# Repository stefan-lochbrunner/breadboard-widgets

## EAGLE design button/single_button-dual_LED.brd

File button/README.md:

[**more info**](https://hackaday.io/project/6332-breadboard-widgets/log/19614-button-w-pull-updown)

#### single button
Small board that incorporates a button and pull-resistor. Can be plugged into power rails. Depending on which side of a breadboard it is plugged in, acts as pull-up or pull-down. Optional footprints for low-pass filter for debouncing.

#### single button with SMD LED breakout
added over complicated LED breakout to utilize board space. Also added arrow to indicate pull direction.

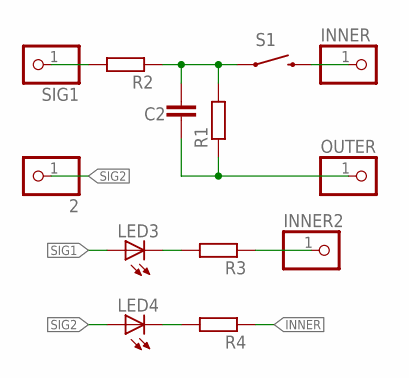
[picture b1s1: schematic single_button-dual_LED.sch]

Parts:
2: PINHD-1X1CB; 1X01-CLEANBIG
C2: CAPACITOR_NPOL-0805; C805
INNER, INNER2: PINHD-1X1CB; 1X01-CLEANBIG
LED3, LED4: LED-0805; LED-805
OUTER: PINHD-1X1CB; 1X01-CLEANBIG
R1, R2, R3, R4: RESISTORR805-0805; R805
S1: SWITCH-MOMENTARY-2PTH; TACTILE-PTH
SIG1: PINHD-1X1CB; 1X01-CLEANBIG

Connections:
INNER: INNER.1, R4.1, S1.3 (2), S1.4 (2)
unnamed: C2.1, R1.2, R2.1, S1.1, S1.2 (1)
unnamed: LED4.C, R4.2
unnamed: LED3.C, R3.2
unnamed: INNER2.1, R3.1
OUTER: C2.2, OUTER.1, R1.1
SIG1: LED3.A, R2.2, SIG1.1
SIG2: 2.1, LED4.A

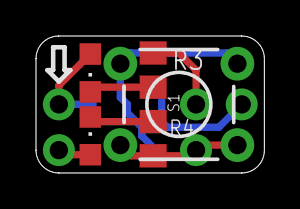
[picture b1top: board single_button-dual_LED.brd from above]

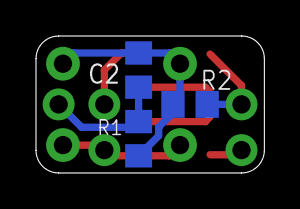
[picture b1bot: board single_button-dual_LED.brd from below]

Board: 2 copper layers, 12.7 x 7.6 mm, 13 parts (3 on the bottom side), 8 nets.

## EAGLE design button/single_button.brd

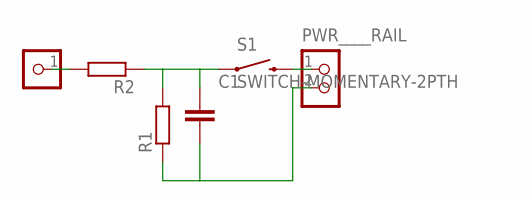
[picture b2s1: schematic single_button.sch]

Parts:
C1: CAPACITOR_NPOL-0805; C805
PWR____RAIL: CON_HEADER_1X02-PTH; M1X2
R1, R2: RESISTORR805-0805; R805
S1: SWITCH-MOMENTARY-2PTH; TACTILE-PTH
SIG: CON_HEADER_1X01-PTH_08_17; M1X2_08_17

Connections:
GND: C1.2, PWR____RAIL.2, R1.1
unnamed: C1.1, R1.2, R2.1, S1.1, S1.2 (1)
unnamed: PWR____RAIL.1, S1.3 (2), S1.4 (2)
unnamed: R2.2, SIG.1

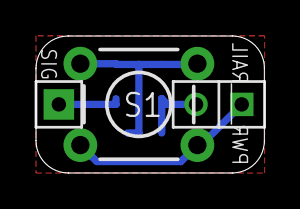
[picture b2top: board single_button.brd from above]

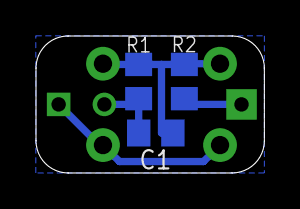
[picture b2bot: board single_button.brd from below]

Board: 2 copper layers, 12.7 x 7.6 mm, 6 parts (3 on the bottom side), 4 nets.

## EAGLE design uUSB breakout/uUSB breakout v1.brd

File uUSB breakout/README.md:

Main functionality is to provide "VUSB circuitry" for AVR microcontrollers. Can also be used as generic uUSB breakout by shorting 68R resistor footprints or as breadboard power supply (supplying 5V).
[**more info**](https://hackaday.io/project/6332-breadboard-widgets/log/19615-uusb-breakout)

####v1

####v2
Allows for supplying different voltages by populating the bottom side with desired regulator. For 5V short solder jumper.

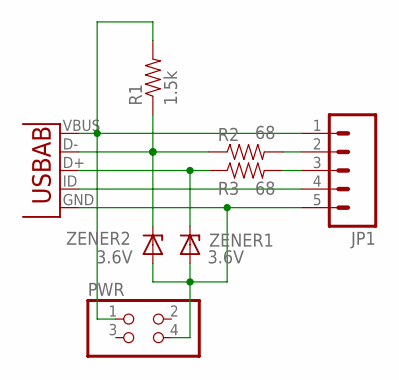
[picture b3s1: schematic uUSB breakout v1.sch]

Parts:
JP1: M05PTH; 1X05
PWR: PINHD-2X2; 2X02
R1: 1.5k; 0805
R2, R3: 68; 0805
UUSB: USB-AB; USB-AB-MICRO-SMD
ZENER1, ZENER2: 3.6V; SOD80C

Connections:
D-: R1.1, R2.1, UUSB.D-, ZENER2.C
GND: JP1.5, PWR.4, UUSB.GND, ZENER1.A, ZENER2.A
ID: JP1.4, UUSB.ID (USBID)
unnamed: JP1.2, R2.2
unnamed: JP1.3, R3.2
unnamed: R3.1, UUSB.D+, ZENER1.C
VCC: JP1.1, PWR.1, R1.2, UUSB.VBUS

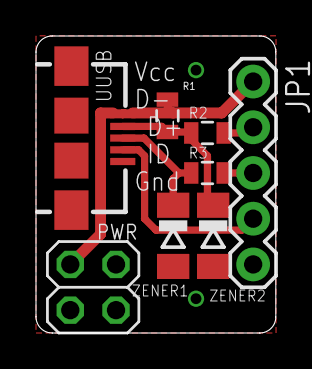
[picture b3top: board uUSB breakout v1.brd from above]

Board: 2 copper layers, 13.3 x 16.5 mm, 8 parts (0 on the bottom side), 7 nets.

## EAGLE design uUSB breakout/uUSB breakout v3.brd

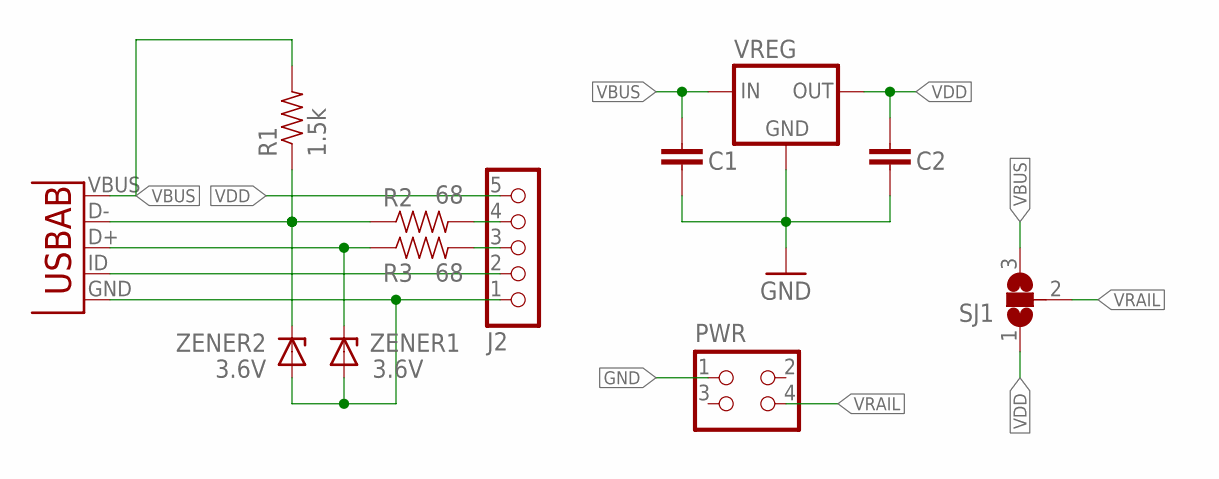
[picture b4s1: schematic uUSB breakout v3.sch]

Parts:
C1, C2: CAPACITOR_NPOL-0805; C805
J2: CON_HEADER_1X05-PTH; M1X5
PWR: CON_HEADER_2X02-PTH; M2X2
R1: 1.5k; 0805
R2, R3: 68; 0805
SJ1: SJ2W; SJ_2
UUSB: USB-AB; USB-AB-MICRO-SMD
VREG: V_REG_MIC2920; SOT223
ZENER1, ZENER2: 3.6V; SOD80C

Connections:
D-: R1.1, R2.1, UUSB.D-, ZENER2.C
GND: C1.2, C2.2, J2.1, PWR.1, UUSB.GND, VREG.2 (GND), VREG.4 (GND), ZENER1.A, ZENER2.A
ID: J2.2, UUSB.ID (USBID)
unnamed: J2.4, R2.2
unnamed: J2.3, R3.2
unnamed: R3.1, UUSB.D+, ZENER1.C
VBUS: C1.1, R1.2, SJ1.3, UUSB.VBUS, VREG.1 (IN)
VDD: C2.1, J2.5, SJ1.1, VREG.3 (OUT)
VRAIL: PWR.4, SJ1.2

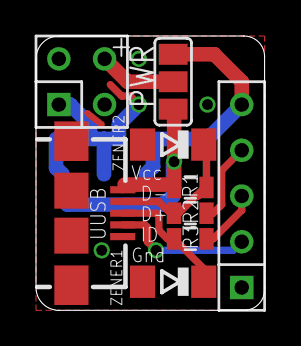
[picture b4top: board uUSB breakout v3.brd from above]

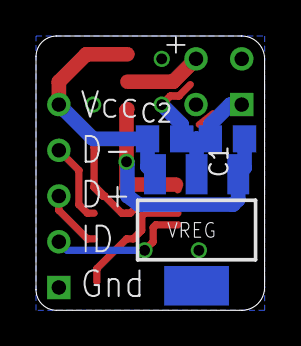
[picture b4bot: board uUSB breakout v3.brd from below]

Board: 2 copper layers, 12.7 x 15.2 mm, 12 parts (3 on the bottom side), 9 nets.

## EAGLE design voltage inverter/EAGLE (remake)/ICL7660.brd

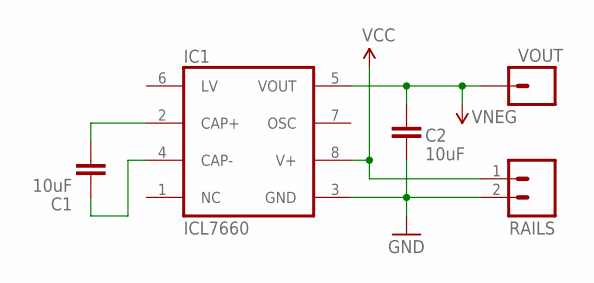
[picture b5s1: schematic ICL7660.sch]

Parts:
C1, C2: 10uF; C1206
IC1: ICL7660; SO08
RAILS: M02PTH; 1X02
VOUT: M01PTH; 1X01

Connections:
GND: C2.2, IC1.3 (GND), RAILS.2
unnamed: C1.2, IC1.2 (CAP+)
unnamed: C1.1, IC1.4 (CAP-)
VCC: IC1.8 (V+), RAILS.1
VNEG: C2.1, IC1.5 (VOUT), VOUT.1

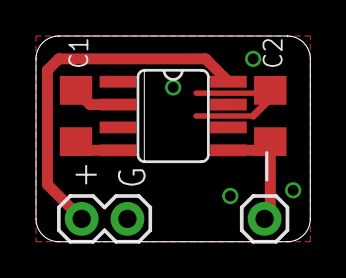
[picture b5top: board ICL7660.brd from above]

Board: 2 copper layers, 15.2 x 11.4 mm, 5 parts (0 on the bottom side), 5 nets.

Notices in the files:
parts and their libraries:
SparkFun-Electromechanical: Licensing: Creative Commons ShareAlike 4.0 International - https://creativecommons.org/licenses/by-sa/4.0
